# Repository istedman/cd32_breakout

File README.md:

# cd32_breakout (Untested)
A breakout/riser board for the CD32, based on the Terriblefire design. Added extra video circuitry, some power supply essentials, PC to Amiga keyboard adaptor and an RS232 serial port. Not tested, released to show correct video circuitry and RS232 port information.

# RGB video information

The design may seem over complex but there is a good reason. The Amiga outputs 5V CMOS levels for it's sync signals. For CRT TVs, not an issue. For modern LCD TV, scan-converters and RGB to HDMI adaptors, it is an issue as the >4V signal is more than the typical 3.3V supply on the LCD TV or converter. On my SCART cable, I added a 680R resistor to attenuate the signals, here I've gone 1 step further, used 5V tolerant, 3.3V logic to drive the correct sync levels. This removes the ~1-2 pixel shift delay that the 680R resistor adds and ensure the rise and fall times are compatible with the VESA VSIS spec. The TI SN74LVC1G97DBVR device is perfect for this application, it is used as a 1 of 2 selector.

U1 and U2 are configurable little logice devices. You can either output HSync and Vsync for monitors/adaptors or CSYNC and 2.5V for RGB SCART. A jumper selects the desired mode of operation, leave off for Minimig SCART and fit to output HSync/Vsync. The AMiga DB23 connector has been disposed of, a 15 way HD (VGA) connector is used as you can easily purchase RGB + Hsync + Vsync cables or a Minimig SCART cable (https://github.com/mist-devel/mist-board/wiki/ScartCable)

The RGB outputs on the CD32 are missing the 75R series resistors, so they have been added here. They are required so that when connectoed to a TV/Monitor/adpator with 75R termination a 0.7V peak signal is seen. Without these resistors the receiver will see a 2x signal (1.4V) which may exceed the dynamic range of some video ADCs/decoders. This causes video colour issues.

IC5 is the 5V to 3.3V LDO converter. C5 must be either a Tantalum, Tantalum polymer or electrolytic capacitor. DO NOT FIT A CERAMIC, it will be unstable. Read this to understand why http://www.ti.com/lit/an/snva167a/snva167a.pdf and enjoy pole/zero analysis :)

# RS232 interface

This is a simple interface, it has TTL level TX/RX and by using IC1, RS232 style serial levels. Connection is via JP2 and was intended for debug using Diagrom. Serial port speed is limited to 56K at best on the CD32.

# PS/2 to Amiga keyboard interface

A clone of sorts, of the IBMKEY25 design from http://aminet.net/docs/hard/epic13.lha
The PIC16C84 is expensive to purchase now, so a PIC16F627A is provisioned for. If you use the RC oscillator and a few tweaks, the original software should work. You could also use the MMKEYBOARD-16f627.HEX from the MMKeyboard archive, this is un-tested. If I get the time, I'll fix the firmware for this.

# PCB layout

A routed but un-tested PCB has been provided. The PCB is 127x62mm, the same size as the DCE SX32 shuttleboard. A fixing hole is provided to screw this board into the CD32.

I've added some power supply decoupling capacitors, the EMC engineer in me demands this and large +5V and ground copper pours fill the PCB. This helps provide a low inductance power supply and increases PCB yield (less chance of over-etching).

FMV signals have been disconnected to save space for routing.

Use at your own risk, I've taken every care with the design but have not tested it as of October 2017.

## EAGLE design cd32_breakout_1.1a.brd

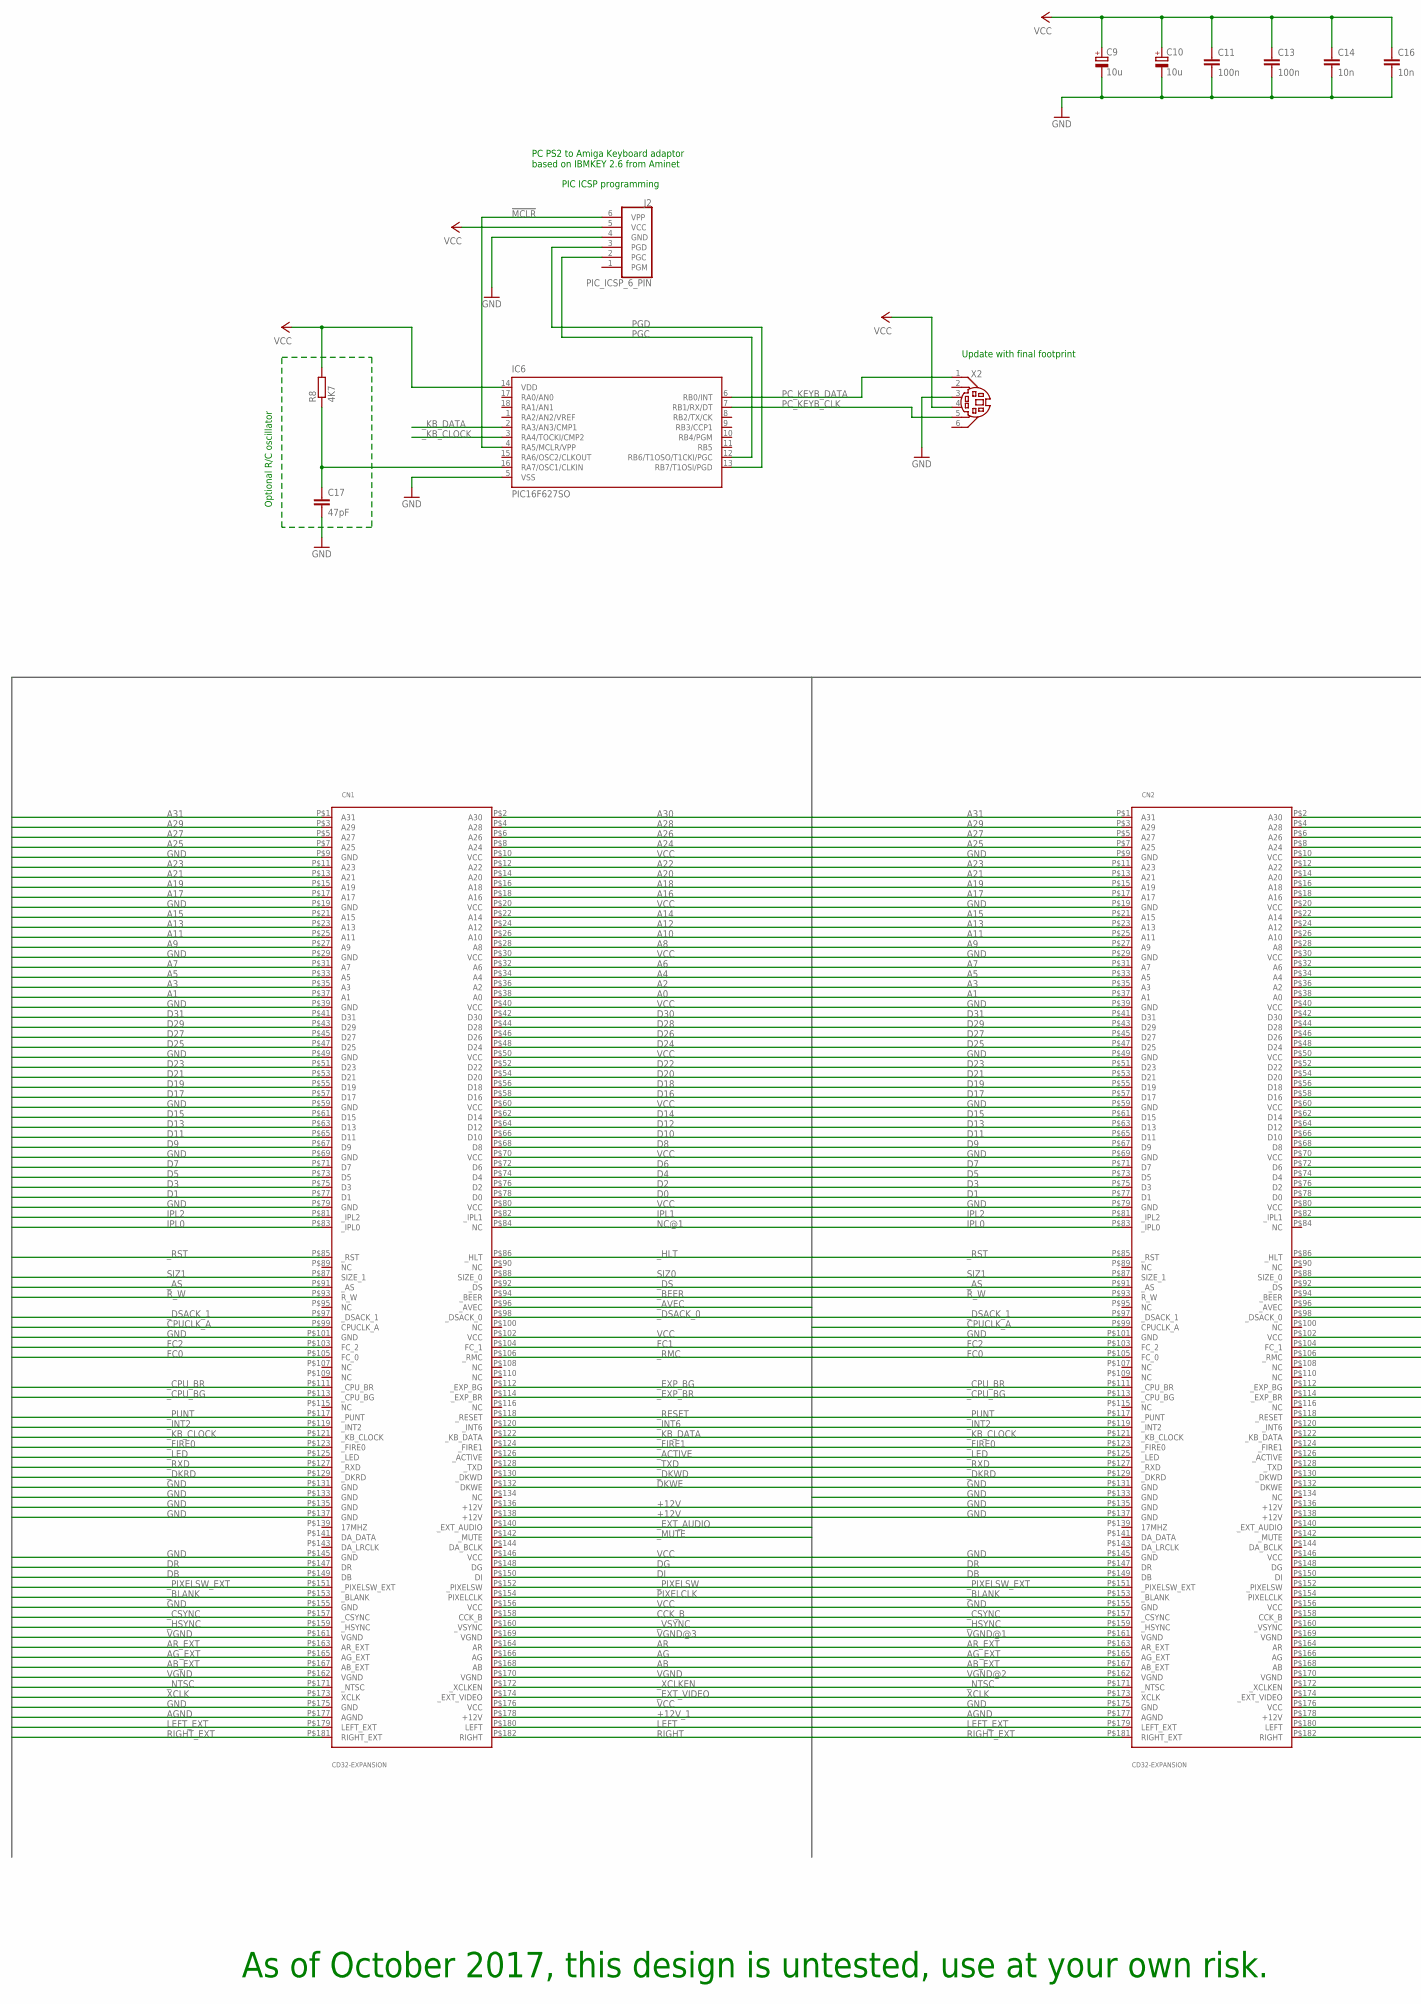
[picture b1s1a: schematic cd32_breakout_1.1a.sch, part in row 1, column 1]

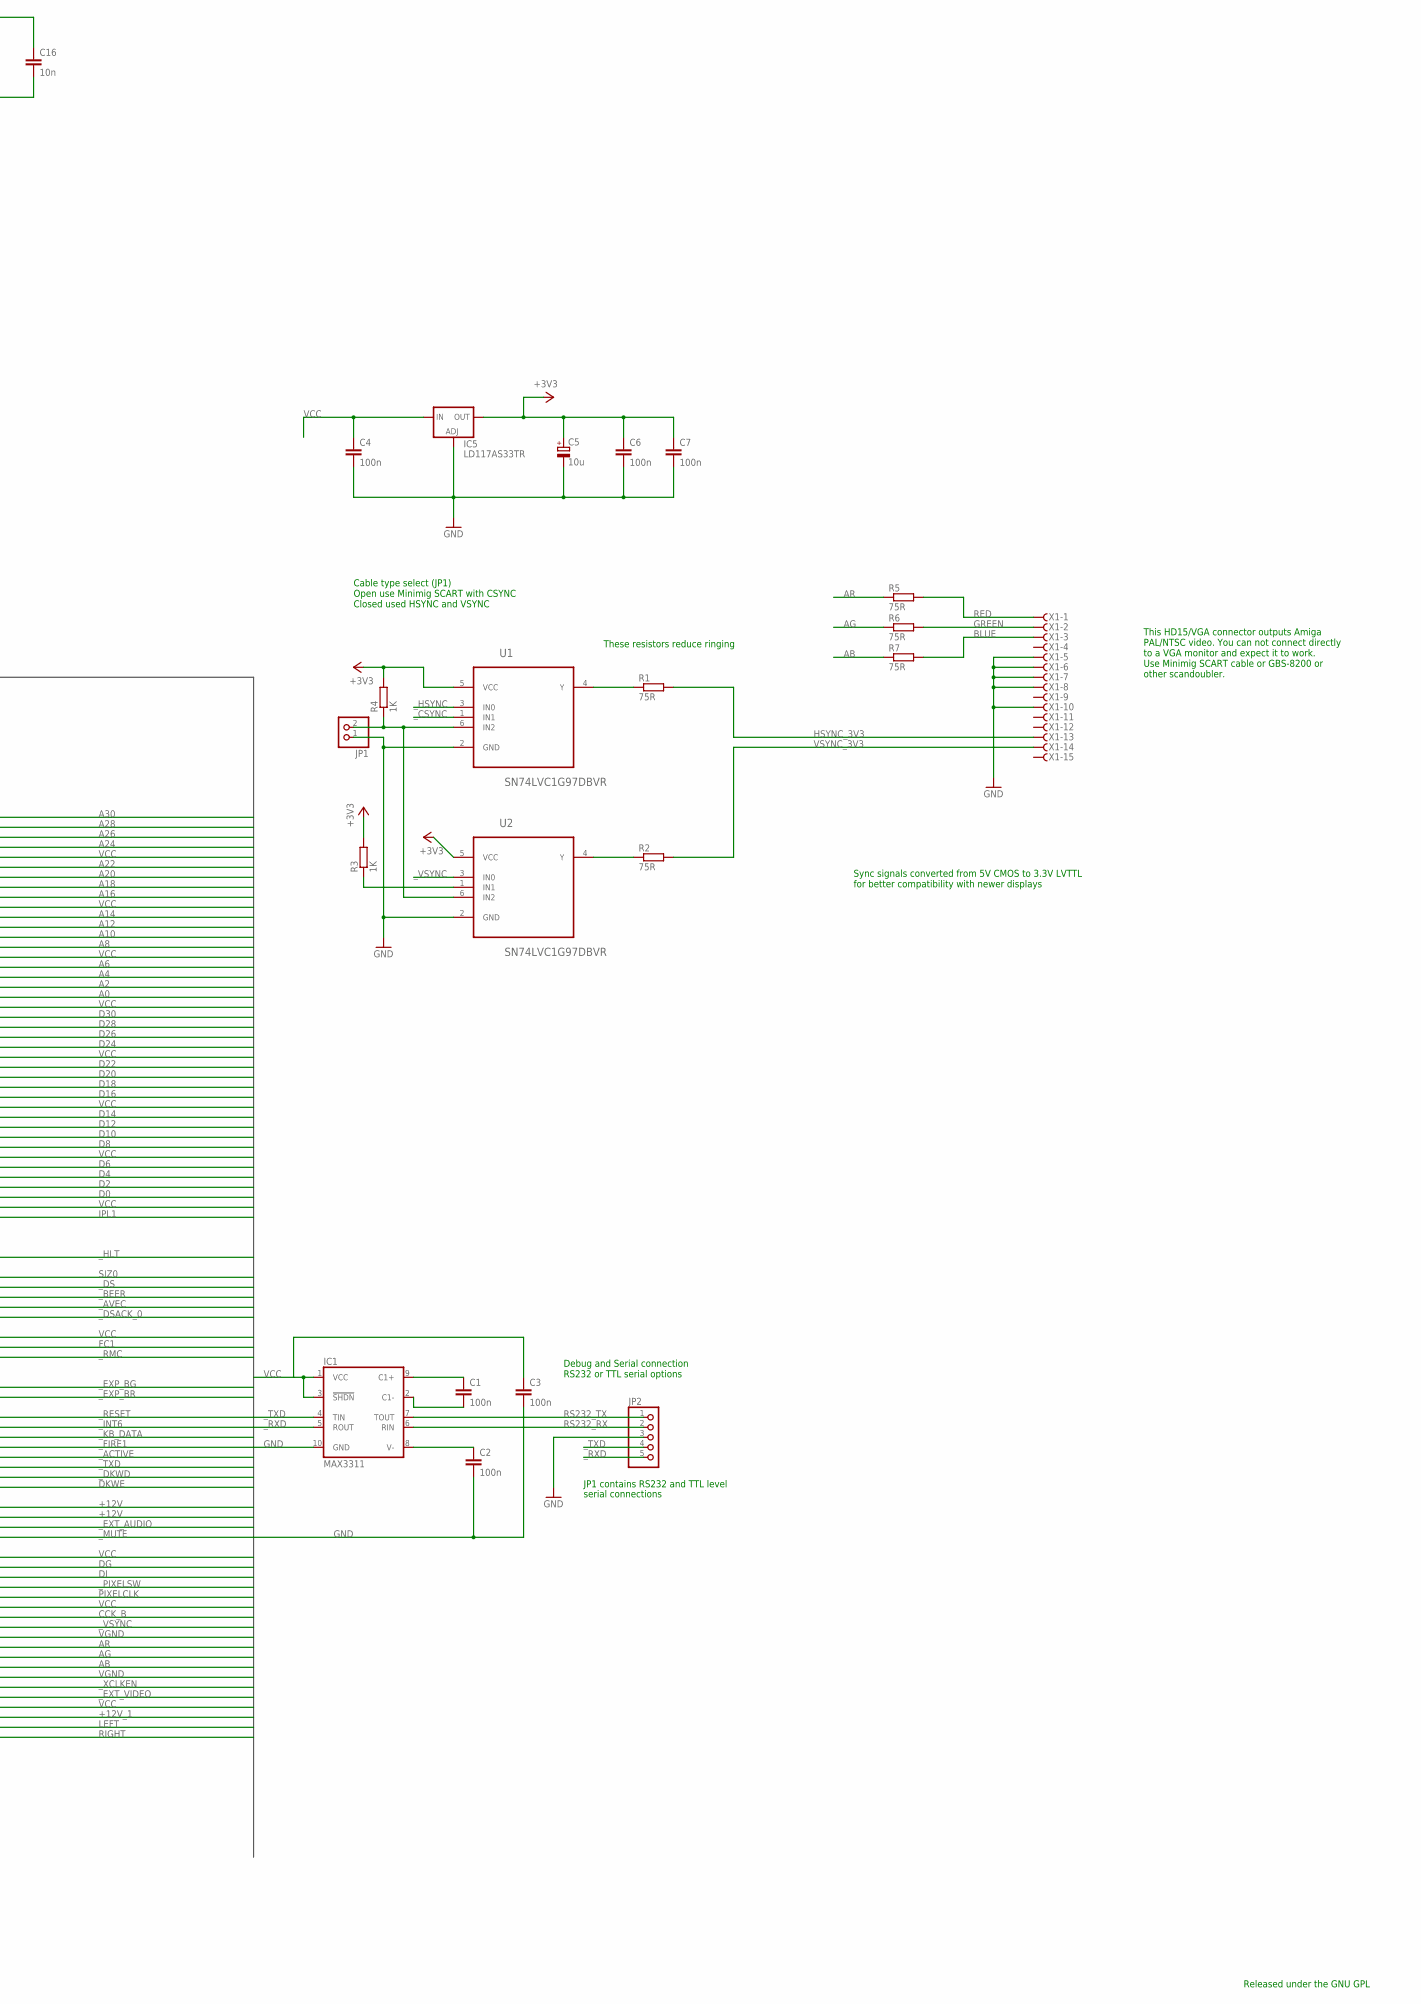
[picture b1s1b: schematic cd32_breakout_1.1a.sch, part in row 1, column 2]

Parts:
C1, C2, C3, C4, C6, C7, C11, C13: 100n; C0603
C5, C9, C10: 10u; PANASONIC_C
C14, C16: 10n; C0603
C17: 47pF; C0603
CN1, CN2: CD32-EXPANSION; CD32_EXPANSION_182_MCA
IC1: MAX3311; UMAX10
IC5: LD117AS33TR; SOT223
IC6: PIC16F627SO; SO-18W
J2: PIC_ICSP_6_PIN; MOLEX-1X6
JP1: PINHD-1X2; 1X02
JP2: PINHD-1X5; 1X05
R1, R2, R5, R6, R7: 75R; R0603
R3, R4: 1K; R0603
R8: 4K7; R0603
U1, U2: SN74LVC1G97DBVR; SOT95P280X145-6N
X1: F15HDVS; HDF15V
X2: MDIN06K

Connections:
!MCLR: IC6.4 (RA5/MCLR/VPP), J2.6 (VPP)
+3V3: C5.+, C6.1, C7.1, IC5.4 (OUT), R3.2, R4.2, U1.5 (VCC), U2.5 (VCC)
+12V: CN1.P$136 (+12V), CN1.P$138 (+12V), CN2.P$136 (+12V), CN2.P$138 (+12V)
+12V_1: CN1.P$178 (+12V), CN2.P$178 (+12V)
A0: CN1.P$38 (A0), CN2.P$38 (A0)
A1: CN1.P$37 (A1), CN2.P$37 (A1)
A2: CN1.P$36 (A2), CN2.P$36 (A2)
A3: CN1.P$35 (A3), CN2.P$35 (A3)
A4: CN1.P$34 (A4), CN2.P$34 (A4)
A5: CN1.P$33 (A5), CN2.P$33 (A5)
A6: CN1.P$32 (A6), CN2.P$32 (A6)
A7: CN1.P$31 (A7), CN2.P$31 (A7)
A8: CN1.P$28 (A8), CN2.P$28 (A8)
A9: CN1.P$27 (A9), CN2.P$27 (A9)
A10: CN1.P$26 (A10), CN2.P$26 (A10)
A11: CN1.P$25 (A11), CN2.P$25 (A11)
A12: CN1.P$24 (A12), CN2.P$24 (A12)
A13: CN1.P$23 (A13), CN2.P$23 (A13)
A14: CN1.P$22 (A14), CN2.P$22 (A14)
A15: CN1.P$21 (A15), CN2.P$21 (A15)
A16: CN1.P$18 (A16), CN2.P$18 (A16)
A17: CN1.P$17 (A17), CN2.P$17 (A17)
A18: CN1.P$16 (A18), CN2.P$16 (A18)
A19: CN1.P$15 (A19), CN2.P$15 (A19)
A20: CN1.P$14 (A20), CN2.P$14 (A20)
A21: CN1.P$13 (A21), CN2.P$13 (A21)
A22: CN1.P$12 (A22), CN2.P$12 (A22)
A23: CN1.P$11 (A23), CN2.P$11 (A23)
A24: CN1.P$8 (A24), CN2.P$8 (A24)
A25: CN1.P$7 (A25), CN2.P$7 (A25)
A26: CN1.P$6 (A26), CN2.P$6 (A26)
A27: CN1.P$5 (A27), CN2.P$5 (A27)
A28: CN1.P$4 (A28), CN2.P$4 (A28)
A29: CN1.P$3 (A29), CN2.P$3 (A29)
A30: CN1.P$2 (A30), CN2.P$2 (A30)
A31: CN1.P$1 (A31), CN2.P$1 (A31)
AB: CN1.P$168 (AB), CN2.P$168 (AB), R7.1
AB_EXT: CN1.P$167 (AB_EXT), CN2.P$167 (AB_EXT)
AG: CN1.P$166 (AG), CN2.P$166 (AG), R6.1
AGND: CN1.P$177 (AGND), CN2.P$177 (AGND)
AG_EXT: CN1.P$165 (AG_EXT), CN2.P$165 (AG_EXT)
AR: CN1.P$164 (AR), CN2.P$164 (AR), R5.1
AR_EXT: CN1.P$163 (AR_EXT), CN2.P$163 (AR_EXT)
BLUE: R7.2, X1.3
CCK_B: CN1.P$158 (CCK_B), CN2.P$158 (CCK_B)
CPUCLK_A: CN1.P$99 (CPUCLK_A), CN2.P$99 (CPUCLK_A)
D0: CN1.P$78 (D0), CN2.P$78 (D0)
D1: CN1.P$77 (D1), CN2.P$77 (D1)
D2: CN1.P$76 (D2), CN2.P$76 (D2)
D3: CN1.P$75 (D3), CN2.P$75 (D3)
D4: CN1.P$74 (D4), CN2.P$74 (D4)
D5: CN1.P$73 (D5), CN2.P$73 (D5)
D6: CN1.P$72 (D6), CN2.P$72 (D6)
D7: CN1.P$71 (D7), CN2.P$71 (D7)
D8: CN1.P$68 (D8), CN2.P$68 (D8)
D9: CN1.P$67 (D9), CN2.P$67 (D9)
D10: CN1.P$66 (D10), CN2.P$66 (D10)
D11: CN1.P$65 (D11), CN2.P$65 (D11)
D12: CN1.P$64 (D12), CN2.P$64 (D12)
D13: CN1.P$63 (D13), CN2.P$63 (D13)
D14: CN1.P$62 (D14), CN2.P$62 (D14)
D15: CN1.P$61 (D15), CN2.P$61 (D15)
D16: CN1.P$58 (D16), CN2.P$58 (D16)
D17: CN1.P$57 (D17), CN2.P$57 (D17)
D18: CN1.P$56 (D18), CN2.P$56 (D18)
D19: CN1.P$55 (D19), CN2.P$55 (D19)
D20: CN1.P$54 (D20), CN2.P$54 (D20)
D21: CN1.P$53 (D21), CN2.P$53 (D21)
D22: CN1.P$52 (D22), CN2.P$52 (D22)
D23: CN1.P$51 (D23), CN2.P$51 (D23)
D24: CN1.P$48 (D24), CN2.P$48 (D24)
D25: CN1.P$47 (D25), CN2.P$47 (D25)
D26: CN1.P$46 (D26), CN2.P$46 (D26)
D27: CN1.P$45 (D27), CN2.P$45 (D27)
D28: CN1.P$44 (D28), CN2.P$44 (D28)
D29: CN1.P$43 (D29), CN2.P$43 (D29)
D30: CN1.P$42 (D30), CN2.P$42 (D30)
D31: CN1.P$41 (D31), CN2.P$41 (D31)
DB: CN1.P$149 (DB), CN2.P$149 (DB)
DG: CN1.P$148 (DG), CN2.P$148 (DG)
DI: CN1.P$150 (DI), CN2.P$150 (DI)
DKWE: CN1.P$132 (DKWE), CN2.P$132 (DKWE)
DR: CN1.P$147 (DR), CN2.P$147 (DR)
FC0: CN1.P$105 (FC_0), CN2.P$105 (FC_0)
FC1: CN1.P$104 (FC_1), CN2.P$104 (FC_1)
FC2: CN1.P$103 (FC_2), CN2.P$103 (FC_2)
GND: C2.2, C3.2, C4.2, C5.-, C6.2, C7.2, C9.-, C10.-, C11.2, C13.2, C14.2, C16.2, C17.2, CN1.P$9 (GND), CN1.P$19 (GND), CN1.P$29 (GND), CN1.P$39 (GND), CN1.P$49 (GND), CN1.P$59 (GND), CN1.P$69 (GND), CN1.P$79 (GND), CN1.P$101 (GND), CN1.P$131 (GND), CN1.P$133 (GND), CN1.P$135 (GND), CN1.P$137 (GND), CN1.P$145 (GND), CN1.P$155 (GND), CN1.P$175 (GND), CN2.P$9 (GND), CN2.P$19 (GND), CN2.P$29 (GND), CN2.P$39 (GND), CN2.P$49 (GND), CN2.P$59 (GND), CN2.P$69 (GND), CN2.P$79 (GND), CN2.P$101 (GND), CN2.P$131 (GND), CN2.P$133 (GND), CN2.P$135 (GND), CN2.P$137 (GND), CN2.P$145 (GND), CN2.P$155 (GND), CN2.P$175 (GND), IC1.10 (GND), IC5.1 (ADJ), IC6.5 (VSS), J2.4 (GND), JP1.1, JP2.3, U1.2 (GND), U2.2 (GND), X1.5, X1.6, X1.7, X1.8, X1.10, X2.3
GREEN: R6.2, X1.2
HSYNC_3V3: R1.2, X1.13
IPL0: CN1.P$83 (_IPL0), CN2.P$83 (_IPL0)
IPL1: CN1.P$82 (_IPL1), CN2.P$82 (_IPL1)
IPL2: CN1.P$81 (_IPL2), CN2.P$81 (_IPL2)
LEFT: CN1.P$180 (LEFT), CN2.P$180 (LEFT)
LEFT_EXT: CN1.P$179 (LEFT_EXT), CN2.P$179 (LEFT_EXT)
unnamed: C1.1, IC1.9 (C1+)
unnamed: C1.2, IC1.2 (C1-)
unnamed: C2.1, IC1.8 (V-)
unnamed: R3.1, U2.1 (IN1)
unnamed: JP1.2, R4.1, U1.6 (IN2), U2.6 (IN2)
unnamed: R1.1, U1.4 (Y)
unnamed: R2.1, U2.4 (Y)
unnamed: C17.1, IC6.16 (RA7/OSC1/CLKIN), R8.1
NC@1: CN1.P$84 (NC)
PC_KEYB_CLK: IC6.7 (RB1/RX/DT), X2.5
PC_KEYB_DATA: IC6.6 (RB0/INT), X2.1
PGC: IC6.12 (RB6/T1OSO/T1CKI/PGC), J2.2 (PGC)
PGD: IC6.13 (RB7/T1OSI/PGD), J2.3 (PGD)
PIXELCLK: CN1.P$154 (PIXELCLK), CN2.P$154 (PIXELCLK)
RED: R5.2, X1.1
RIGHT: CN1.P$182 (RIGHT), CN2.P$182 (RIGHT)
RIGHT_EXT: CN1.P$181 (RIGHT_EXT), CN2.P$181 (RIGHT_EXT)
RS232_RX: IC1.6 (RIN), JP2.2
RS232_TX: IC1.7 (TOUT), JP2.1
R_W: CN1.P$93 (R_W), CN2.P$93 (R_W)
SIZ0: CN1.P$88 (SIZE_0), CN2.P$88 (SIZE_0)
SIZ1: CN1.P$87 (SIZE_1), CN2.P$87 (SIZE_1)
VCC: C3.1, C4.1, C9.+, C10.+, C11.1, C13.1, C14.1, C16.1, CN1.P$10 (VCC), CN1.P$20 (VCC), CN1.P$30 (VCC), CN1.P$40 (VCC), CN1.P$50 (VCC), CN1.P$60 (VCC), CN1.P$70 (VCC), CN1.P$80 (VCC), CN1.P$102 (VCC), CN1.P$146 (VCC), CN1.P$156 (VCC), CN1.P$176 (VCC), CN2.P$10 (VCC), CN2.P$20 (VCC), CN2.P$30 (VCC), CN2.P$40 (VCC), CN2.P$50 (VCC), CN2.P$60 (VCC), CN2.P$70 (VCC), CN2.P$80 (VCC), CN2.P$102 (VCC), CN2.P$146 (VCC), CN2.P$156 (VCC), CN2.P$176 (VCC), IC1.1 (VCC), IC1.3 (!SHDN), IC5.3 (IN), IC6.14 (VDD), J2.5 (VCC), R8.2, X2.4
VGND: CN1.P$161 (VGND), CN1.P$162 (VGND), CN1.P$170 (VGND), CN2.P$169 (VGND), CN2.P$170 (VGND)
VGND@1: CN2.P$161 (VGND)
VGND@2: CN2.P$162 (VGND)
VGND@3: CN1.P$169 (VGND)
VSYNC_3V3: R2.2, X1.14
XCLK: CN1.P$173 (XCLK), CN2.P$173 (XCLK)
_ACTIVE: CN1.P$126 (_ACTIVE), CN2.P$126 (_ACTIVE)
_AS: CN1.P$91 (_AS), CN2.P$91 (_AS)
_AVEC: CN1.P$96 (_AVEC), CN2.P$96 (_AVEC)
_BEER: CN1.P$94 (_BEER), CN2.P$94 (_BEER)
_BLANK: CN1.P$153 (_BLANK), CN2.P$153 (_BLANK)
_CPU_BG: CN1.P$113 (_CPU_BG), CN2.P$113 (_CPU_BG)
_CPU_BR: CN1.P$111 (_CPU_BR), CN2.P$111 (_CPU_BR)
_CSYNC: CN1.P$157 (_CSYNC), CN2.P$157 (_CSYNC), U1.1 (IN1)
_DKRD: CN1.P$129 (_DKRD), CN2.P$129 (_DKRD)
_DKWD: CN1.P$130 (_DKWD), CN2.P$130 (_DKWD)
_DS: CN1.P$92 (_DS), CN2.P$92 (_DS)
_DSACK_0: CN1.P$98 (_DSACK_0), CN2.P$98 (_DSACK_0)
_DSACK_1: CN1.P$97 (_DSACK_1), CN2.P$97 (_DSACK_1)
_EXP_BG: CN1.P$112 (_EXP_BG), CN2.P$112 (_EXP_BG)
_EXP_BR: CN1.P$114 (_EXP_BR), CN2.P$114 (_EXP_BR)
_EXT_AUDIO: CN1.P$140 (_EXT_AUDIO), CN2.P$140 (_EXT_AUDIO)
_EXT_VIDEO: CN1.P$174 (_EXT_VIDEO), CN2.P$174 (_EXT_VIDEO)
_FIRE0: CN1.P$123 (_FIRE0), CN2.P$123 (_FIRE0)
_FIRE1: CN1.P$124 (_FIRE1), CN2.P$124 (_FIRE1)
_HLT: CN1.P$86 (_HLT), CN2.P$86 (_HLT)
_HSYNC: CN1.P$159 (_HSYNC), CN2.P$159 (_HSYNC), U1.3 (IN0)
_INT2: CN1.P$119 (_INT2), CN2.P$119 (_INT2)
_INT6: CN1.P$120 (_INT6), CN2.P$120 (_INT6)
_KB_CLOCK: CN1.P$121 (_KB_CLOCK), CN2.P$121 (_KB_CLOCK), IC6.3 (RA4/TOCKI/CMP2)
_KB_DATA: CN1.P$122 (_KB_DATA), CN2.P$122 (_KB_DATA), IC6.2 (RA3/AN3/CMP1)
_LED: CN1.P$125 (_LED), CN2.P$125 (_LED)
_MUTE: CN1.P$142 (_MUTE), CN2.P$142 (_MUTE)
_NTSC: CN1.P$171 (_NTSC), CN2.P$171 (_NTSC)
_PIXELSW: CN1.P$152 (_PIXELSW), CN2.P$152 (_PIXELSW)
_PIXELSW_EXT: CN1.P$151 (_PIXELSW_EXT), CN2.P$151 (_PIXELSW_EXT)
_PUNT: CN1.P$117 (_PUNT), CN2.P$117 (_PUNT)
_RESET: CN1.P$118 (_RESET), CN2.P$118 (_RESET)
_RMC: CN1.P$106 (_RMC), CN2.P$106 (_RMC)
_RST: CN1.P$85 (_RST), CN2.P$85 (_RST)
_RXD: CN1.P$127 (_RXD), CN2.P$127 (_RXD), IC1.5 (ROUT), JP2.5
_TXD: CN1.P$128 (_TXD), CN2.P$128 (_TXD), IC1.4 (TIN), JP2.4
_VSYNC: CN1.P$160 (_VSYNC), CN2.P$160 (_VSYNC), U2.3 (IN0)
_XCLKEN: CN1.P$172 (_XCLKEN), CN2.P$172 (_XCLKEN)

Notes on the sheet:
JP1 contains RS232 and TTL level
serial connections
Cable type select (JP1) Open use Minimig SCART with CSYNC Closed used HSYNC and VSYNC
Debug and Serial connection RS232 or TTL serial options
Update with final footprint
PIC ICSP programming
PC PS2 to Amiga Keyboard adaptor based on IBMKEY 2.6 from Aminet
This HD15/VGA connector outputs Amiga PAL/NTSC video. You can not connect directly to a VGA monitor and expect it to work. Use Minimig SCART cable or GBS-8200 or other scandoubler.
Sync signals converted from 5V CMOS to 3.3V LVTTL for better compatibility with newer displays
These resistors reduce ringing
Optional R/C oscillator
Released under the GNU GPL
As of October 2017, this design is untested, use at your own risk.

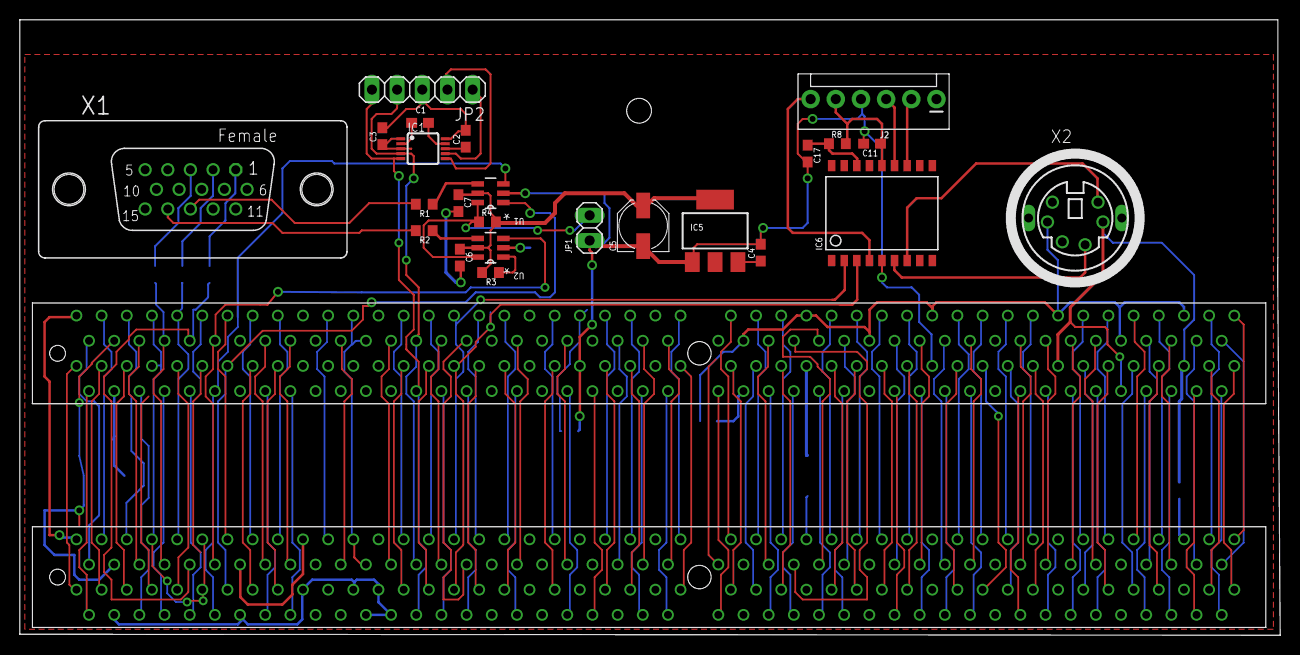
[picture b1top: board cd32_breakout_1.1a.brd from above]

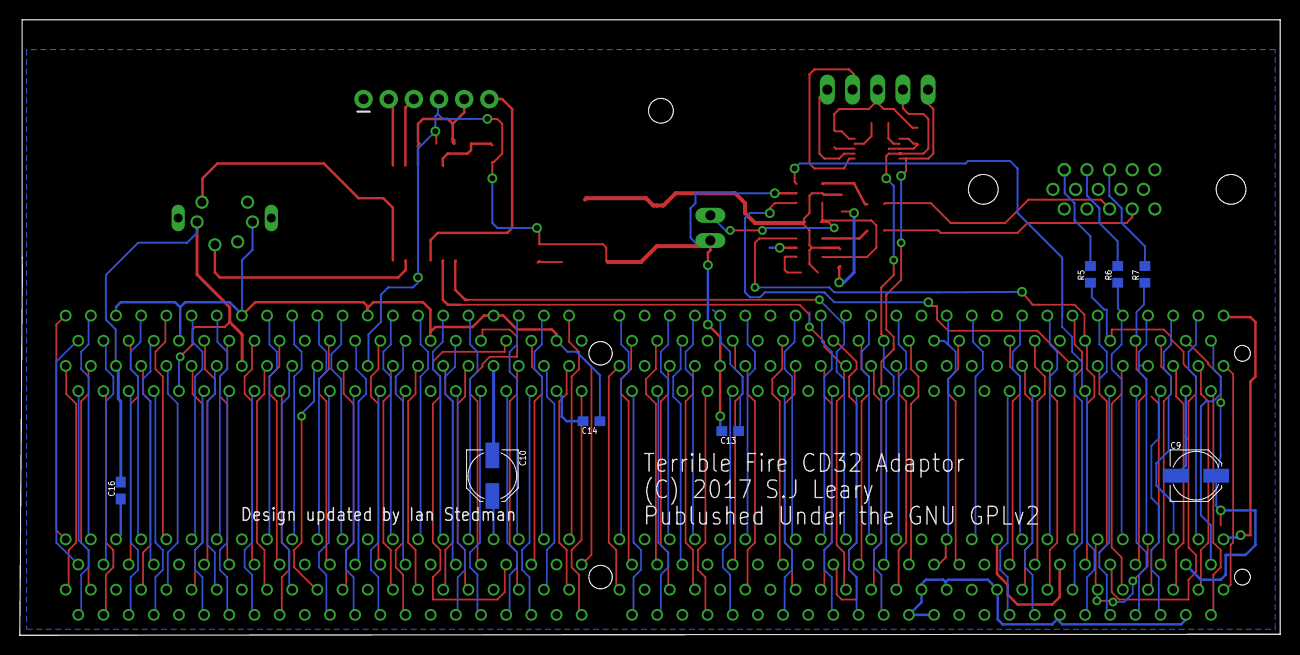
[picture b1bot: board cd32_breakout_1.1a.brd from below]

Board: 2 copper layers, 127.2 x 62.1 mm, 34 parts (8 on the bottom side), 157 nets.

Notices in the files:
cd32_breakout_1.1a.brd:
(C) 2017 S.J Leary
Publushed Under the GNU GPLv2
parts and their libraries:
SparkFun-Connectors: Licensing: Creative Commons ShareAlike 4.0 International - https://creativecommons.org/licenses/by-sa/4.0
